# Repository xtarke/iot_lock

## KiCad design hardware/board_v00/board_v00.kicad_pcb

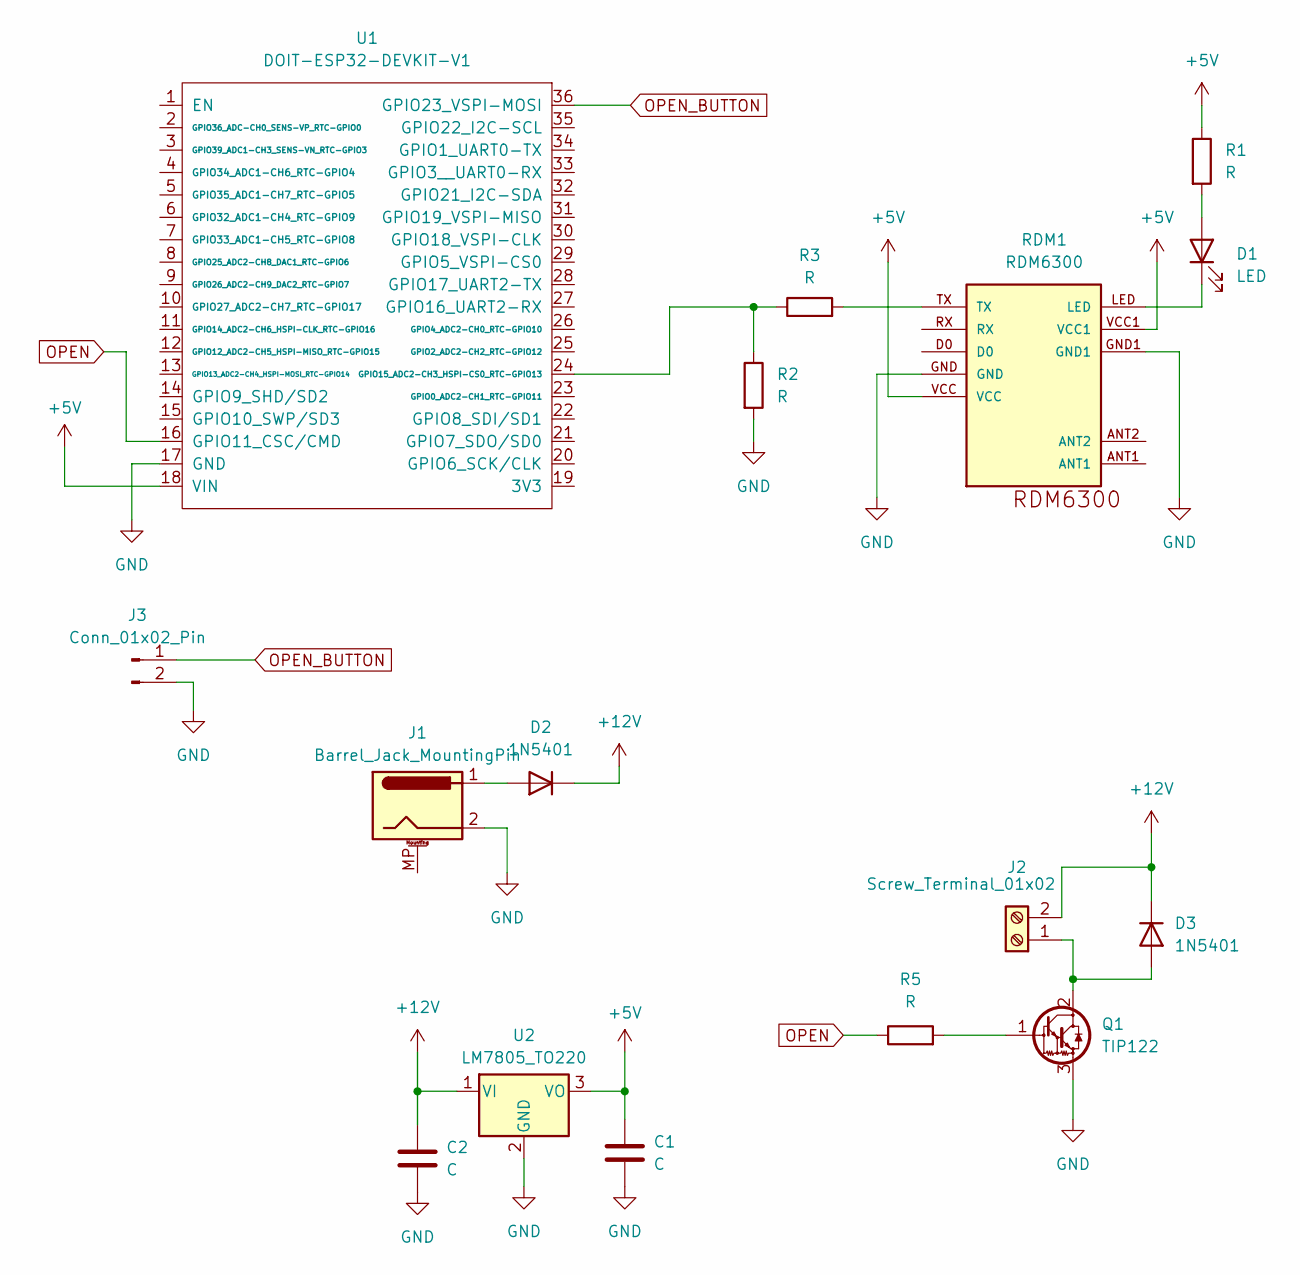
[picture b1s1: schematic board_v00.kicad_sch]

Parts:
C1, C2: C; C_0805_2012Metric_Pad1.18x1.45mm_HandSolder
D1: LED; LED_D3.0mm
D2, D3: 1N5401; D_DO-201AD_P15.24mm_Horizontal
J1: Barrel_Jack_MountingPin; BarrelJack_Horizontal
J2: Screw_Terminal_01x02; TerminalBlock_Phoenix_MKDS-1,5-2-5.08_1x02_P5.08mm_Horizont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
J3: Conn_01x02_Pin; PinHeader_1x02_P2.54mm_Vertical
Q1: TIP122; TO-220-3_Horizontal_TabDown
R1, R2, R3, R5: R; R_0805_2012Metric_Pad1.20x1.40mm_HandSolder
RDM1: RDM6300
U1: DOIT-ESP32-DEVKIT-V1; ESP32-DOIT-DEVKIT
U2: LM7805_TO220; TO-220-3_Horizontal_TabDown

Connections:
+5V: C1.1, R1.1, RDM1.VCC, RDM1.VCC1, U1.18 (VIN), U2.3 (VO)
+12V: C2.1, D2.1 (K), D3.1 (K), J2.2, U2.1 (VI)
GND: C1.2, C2.2, J1.2, J3.2, Q1.3 (E), R2.2, RDM1.GND, RDM1.GND1, U1.17 (GND), U2.2 (GND)
unnamed: D1.2 (A), R1.2
unnamed: D1.1 (K), RDM1.LED
unnamed: D2.2 (A), J1.1
unnamed: D3.2 (A), J2.1, Q1.2 (C)
unnamed: Q1.1 (B), R5.2
unnamed: R3.2, RDM1.TX
unnamed: R2.1, R3.1, U1.24 (GPIO15_ADC2-CH3_HSPI-CS0_RTC-GPIO13)
OPEN: R5.1, U1.16 (GPIO11_CSC/CMD)
OPEN_BUTTON: J3.1, U1.36 (GPIO23_VSPI-MOSI)

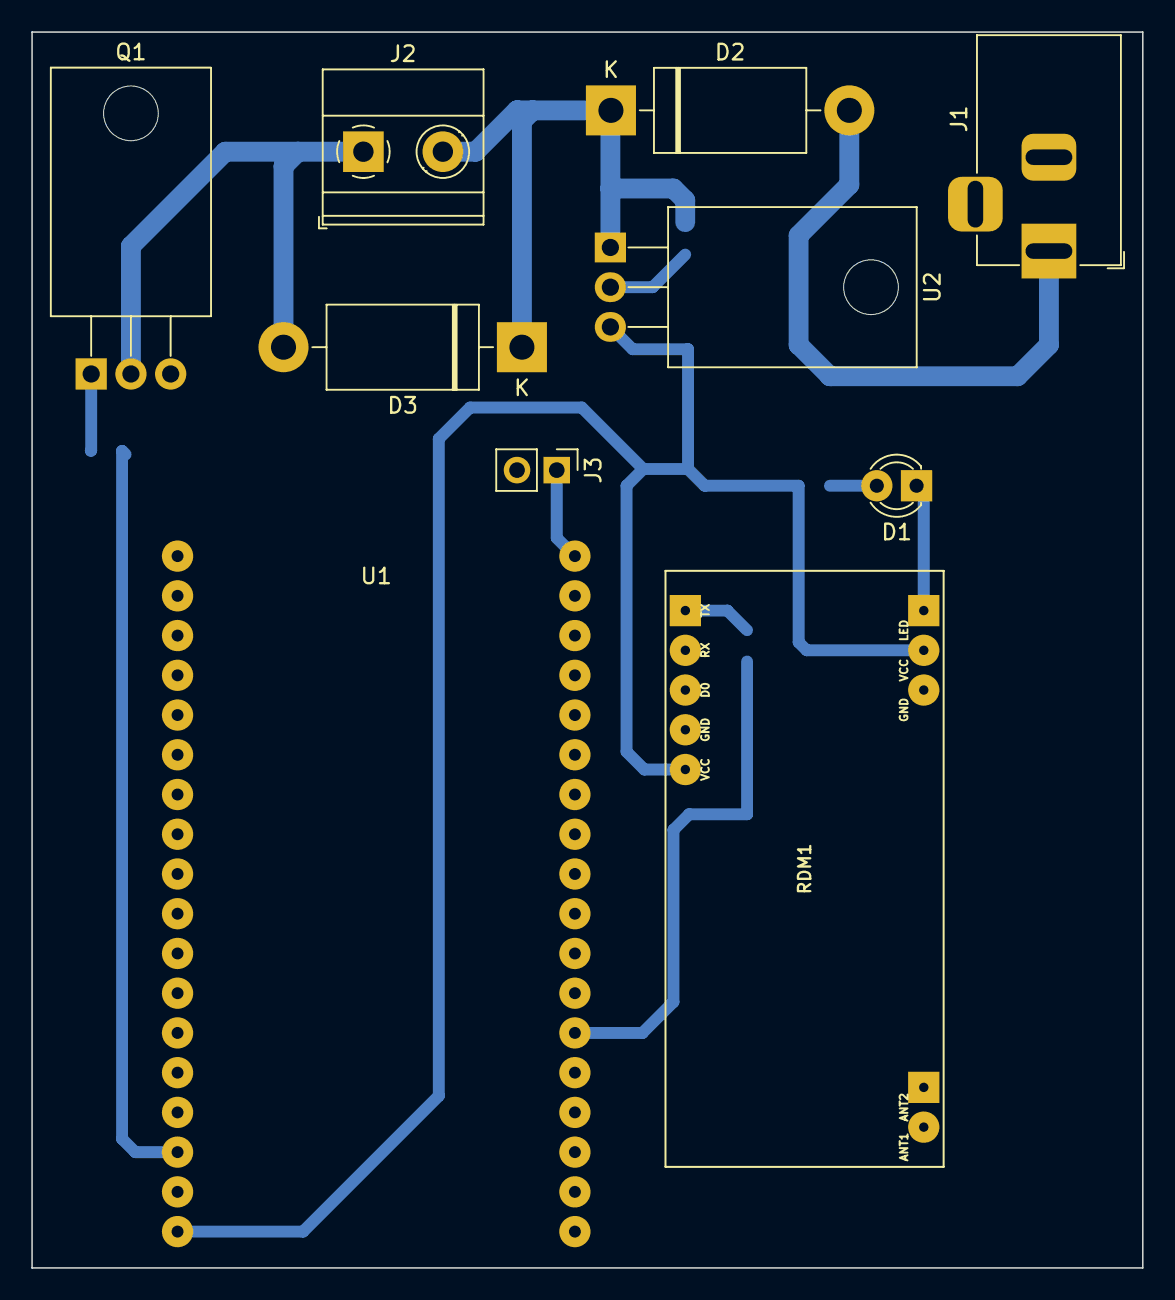
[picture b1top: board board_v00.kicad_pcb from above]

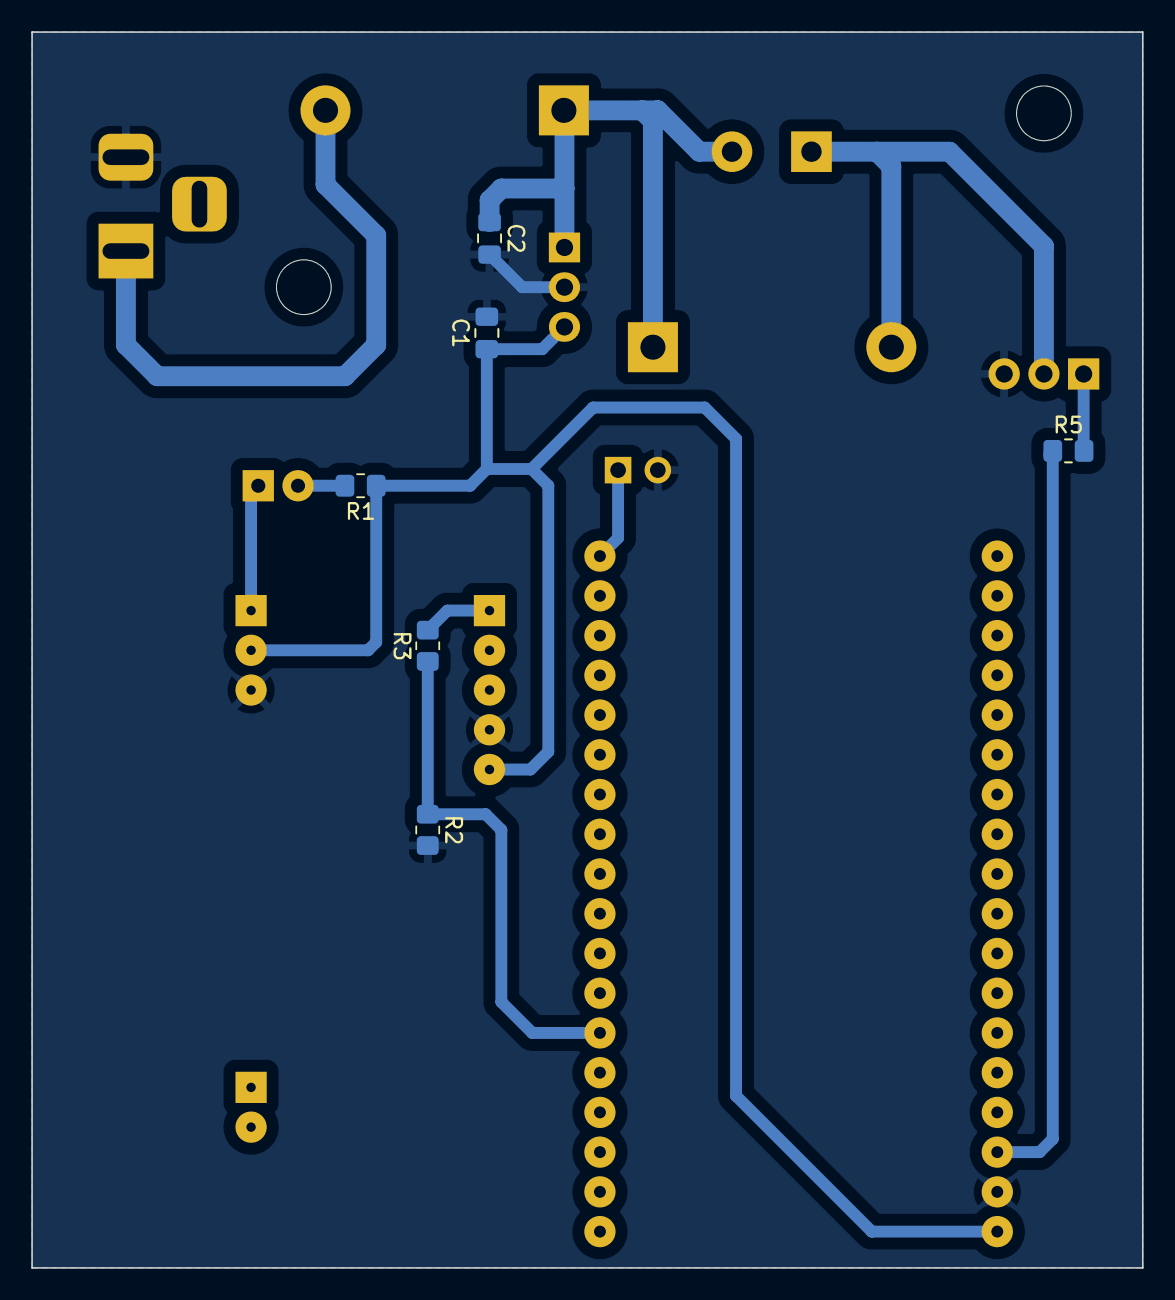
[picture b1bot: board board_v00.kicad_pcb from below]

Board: 2 copper layers, 71.0 x 79.0 mm, 16 parts (6 on the bottom side), 12 nets.

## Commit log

2022-07-28 Added some classes
2022-07-29 Rdm6300 class implementation
2022-08-15 Implemented tag protocol
2022-08-16 Added Time interface.
2022-08-17 Try to fix uart sync
2022-08-18 Fix reading, added task suspension
2023-12-14 Added mqqt class
2023-12-15 Mqqt test
2023-12-18 Added tag class
2023-12-18 Removing trash
2023-12-18 removed sdk config
2023-12-18 added sdk defaults
2023-12-19 Added code documentation
2024-02-08 Added new class and hardware
2024-02-09 Added mqtt logs
2024-02-09 Added mqtt publish mutex
2025-02-07 Updated mqtt topics and msgs
